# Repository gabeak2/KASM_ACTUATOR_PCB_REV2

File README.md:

A PCBA to drive voice coil actuators at Keck and University of Hawaii at Hilo.  Work done as part of my MS ECE Thesis at Johns Hopkins.  Please enjoy this beautiful glamor shot of my boards !

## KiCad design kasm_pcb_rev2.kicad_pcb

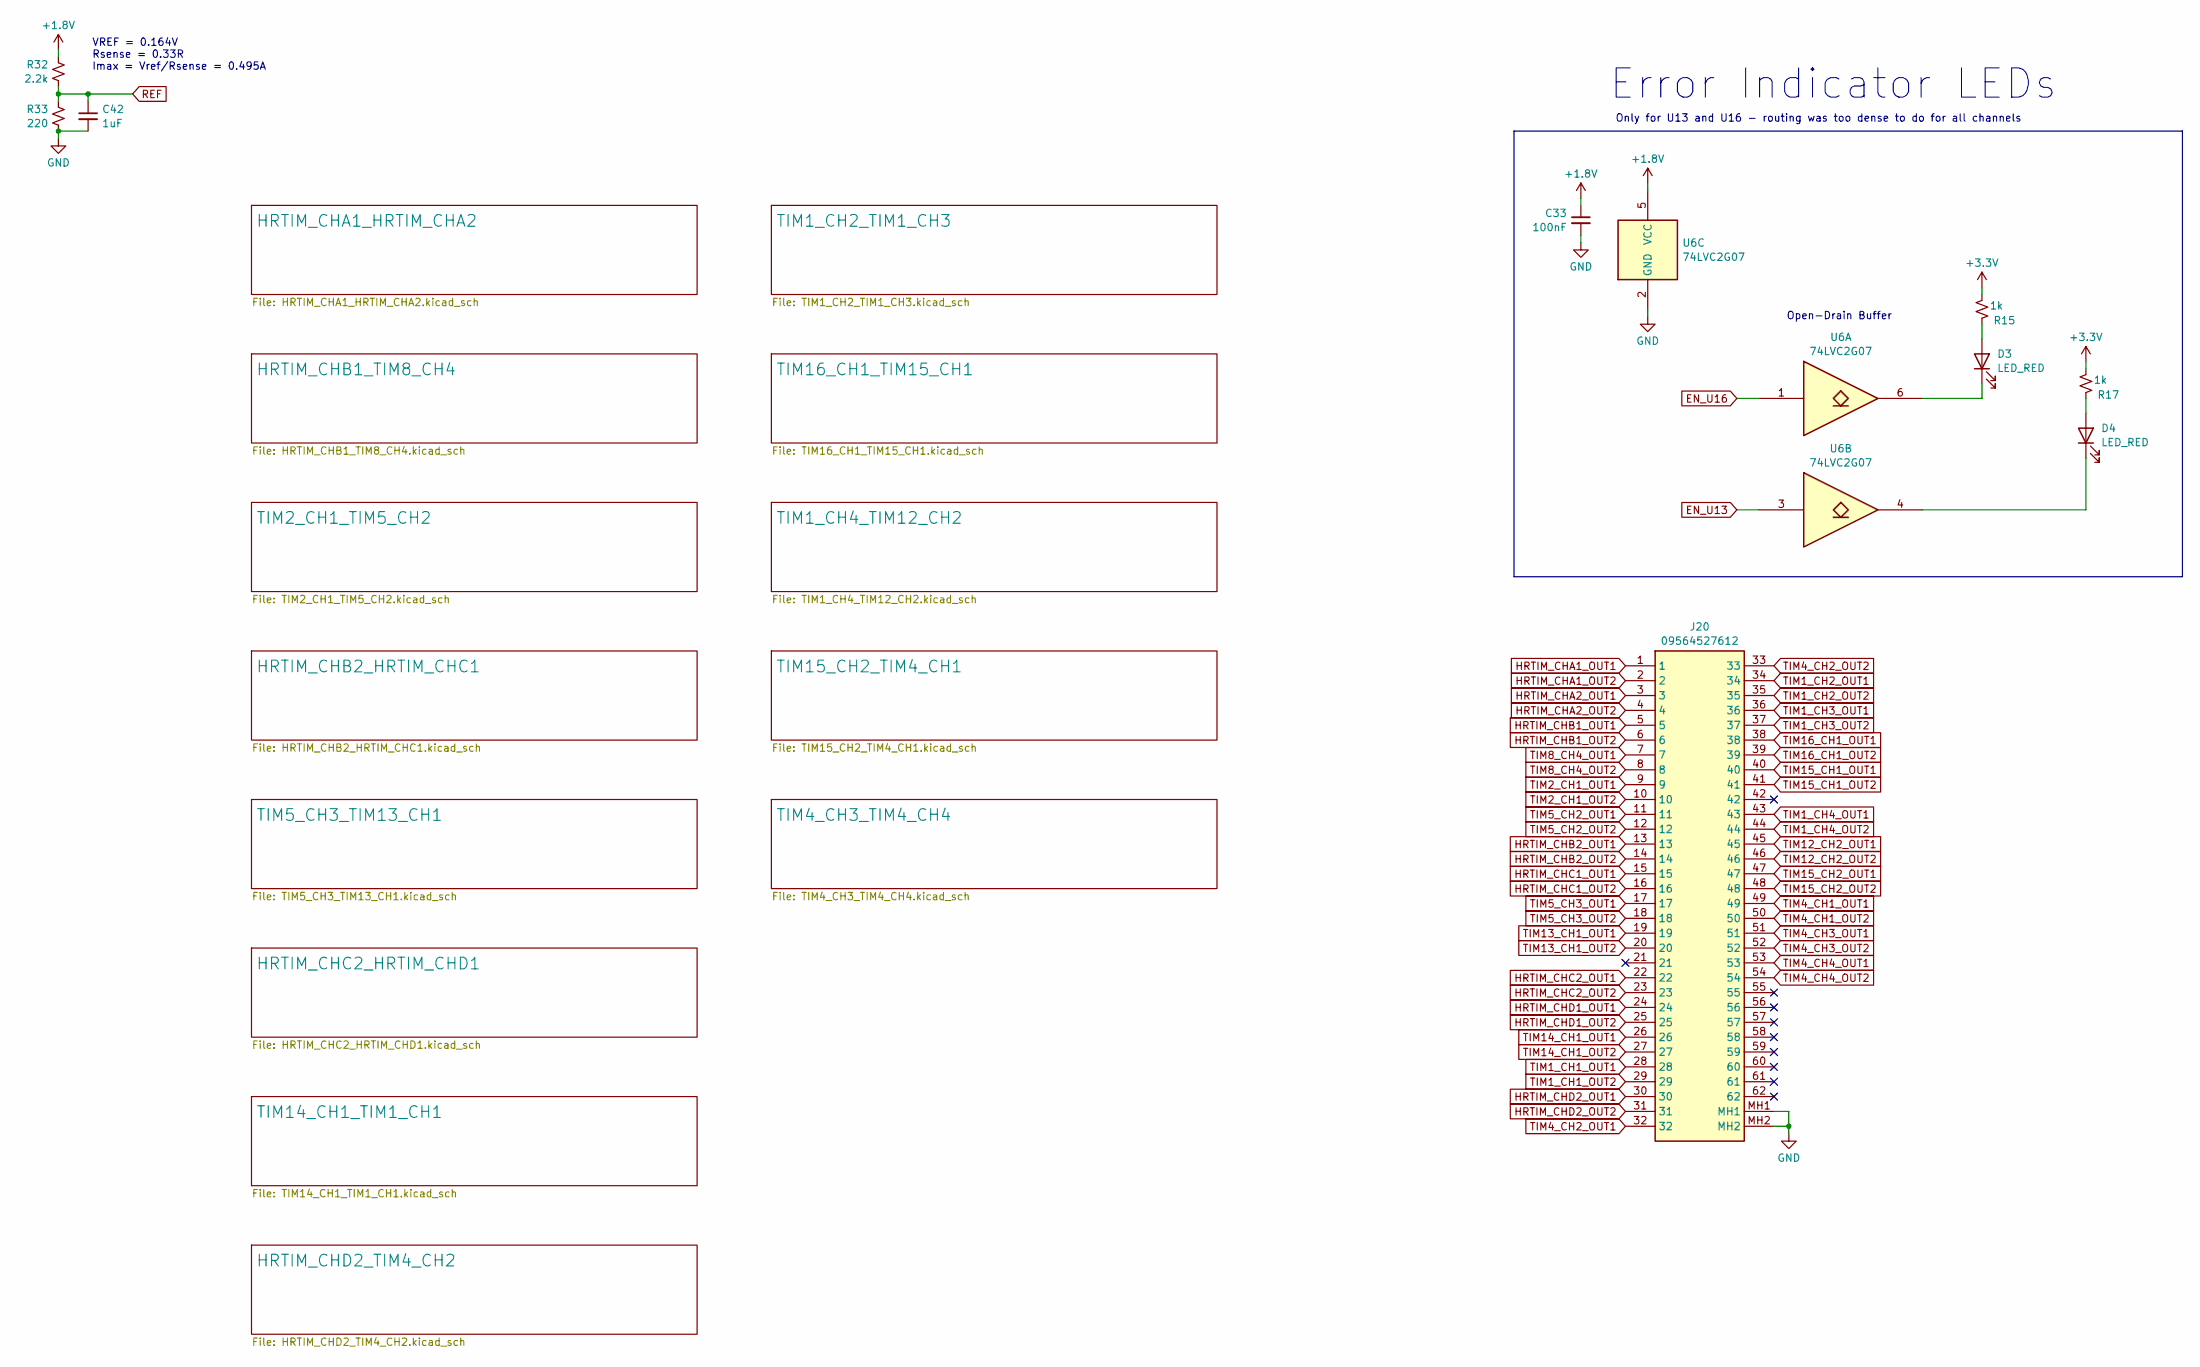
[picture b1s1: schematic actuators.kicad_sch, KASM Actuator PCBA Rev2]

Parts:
C33: 100nF; C_0402_1005Metric; LCSC C1525
C42: 1uF; C_0402_1005Metric; LCSC C52923
D3, D4: LED_RED; LED_0603_1608Metric; LCSC C2286
J20: 09564527612; Manufacturer_Part_Number 09564527612; Mouser Part Number 617-09-56-452-7612
R15, R17: 1k; R_0402_1005Metric; LCSC C11702
R32: 2.2k; R_0402_1005Metric; LCSC C25879
R33: 220; R_0402_1005Metric; LCSC C25091
U6: 74LVC2G07; SOT-23-6; LCSC C37708

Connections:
+1.8V: C33.1, R32.1, U6.5 (VCC); also elsewhere on the board
+3.3V: R15.1, R17.1; also elsewhere on the board
EN_U13: U6.3; also elsewhere on the board
EN_U16: U6.1; also elsewhere on the board
GND: C33.2, C42.2, J20.MH1, J20.MH2, R33.2, U6.2 (GND); also elsewhere on the board
HRTIM_CHA1_OUT1: J20.1; also elsewhere on the board
HRTIM_CHA1_OUT2: J20.2; also elsewhere on the board
HRTIM_CHA2_OUT1: J20.3; also elsewhere on the board
HRTIM_CHA2_OUT2: J20.4; also elsewhere on the board
HRTIM_CHB1_OUT1: J20.5; also elsewhere on the board
HRTIM_CHB1_OUT2: J20.6; also elsewhere on the board
HRTIM_CHB2_OUT1: J20.13; also elsewhere on the board
HRTIM_CHB2_OUT2: J20.14; also elsewhere on the board
HRTIM_CHC1_OUT1: J20.15; also elsewhere on the board
HRTIM_CHC1_OUT2: J20.16; also elsewhere on the board
HRTIM_CHC2_OUT1: J20.22; also elsewhere on the board
HRTIM_CHC2_OUT2: J20.23; also elsewhere on the board
HRTIM_CHD1_OUT1: J20.24; also elsewhere on the board
HRTIM_CHD1_OUT2: J20.25; also elsewhere on the board
HRTIM_CHD2_OUT1: J20.30; also elsewhere on the board
HRTIM_CHD2_OUT2: J20.31; also elsewhere on the board
unnamed: D3.2 (A), R15.2
unnamed: D3.1 (K), U6.6
unnamed: D4.2 (A), R17.2
unnamed: D4.1 (K), U6.4
REF: C42.1, R32.2, R33.1; also elsewhere on the board
TIM1_CH1_OUT1: J20.28; also elsewhere on the board
TIM1_CH1_OUT2: J20.29; also elsewhere on the board
TIM1_CH2_OUT1: J20.34; also elsewhere on the board
TIM1_CH2_OUT2: J20.35; also elsewhere on the board
TIM1_CH3_OUT1: J20.36; also elsewhere on the board
TIM1_CH3_OUT2: J20.37; also elsewhere on the board
TIM1_CH4_OUT1: J20.43; also elsewhere on the board
TIM1_CH4_OUT2: J20.44; also elsewhere on the board
TIM2_CH1_OUT1: J20.9; also elsewhere on the board
TIM2_CH1_OUT2: J20.10; also elsewhere on the board
TIM4_CH1_OUT1: J20.49; also elsewhere on the board
TIM4_CH1_OUT2: J20.50; also elsewhere on the board
TIM4_CH2_OUT1: J20.32; also elsewhere on the board
TIM4_CH2_OUT2: J20.33; also elsewhere on the board
TIM4_CH3_OUT1: J20.51; also elsewhere on the board
TIM4_CH3_OUT2: J20.52; also elsewhere on the board
TIM4_CH4_OUT1: J20.53; also elsewhere on the board
TIM4_CH4_OUT2: J20.54; also elsewhere on the board
TIM5_CH2_OUT1: J20.11; also elsewhere on the board
TIM5_CH2_OUT2: J20.12; also elsewhere on the board
TIM5_CH3_OUT1: J20.17; also elsewhere on the board
TIM5_CH3_OUT2: J20.18; also elsewhere on the board
TIM8_CH4_OUT1: J20.7; also elsewhere on the board
TIM8_CH4_OUT2: J20.8; also elsewhere on the board
TIM12_CH2_OUT1: J20.45; also elsewhere on the board
TIM12_CH2_OUT2: J20.46; also elsewhere on the board
TIM13_CH1_OUT1: J20.19; also elsewhere on the board
TIM13_CH1_OUT2: J20.20; also elsewhere on the board
TIM14_CH1_OUT1: J20.26; also elsewhere on the board
TIM14_CH1_OUT2: J20.27; also elsewhere on the board
TIM15_CH1_OUT1: J20.40; also elsewhere on the board
TIM15_CH1_OUT2: J20.41; also elsewhere on the board
TIM15_CH2_OUT1: J20.47; also elsewhere on the board
TIM15_CH2_OUT2: J20.48; also elsewhere on the board
TIM16_CH1_OUT1: J20.38; also elsewhere on the board
TIM16_CH1_OUT2: J20.39; also elsewhere on the board

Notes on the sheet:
Only for U13 and U16 - routing was too dense to do for all channels
Error Indicator LEDs
Open-Drain Buffer
VREF = 0.164V Rsense = 0.33R Imax = Vref/Rsense = 0.495A

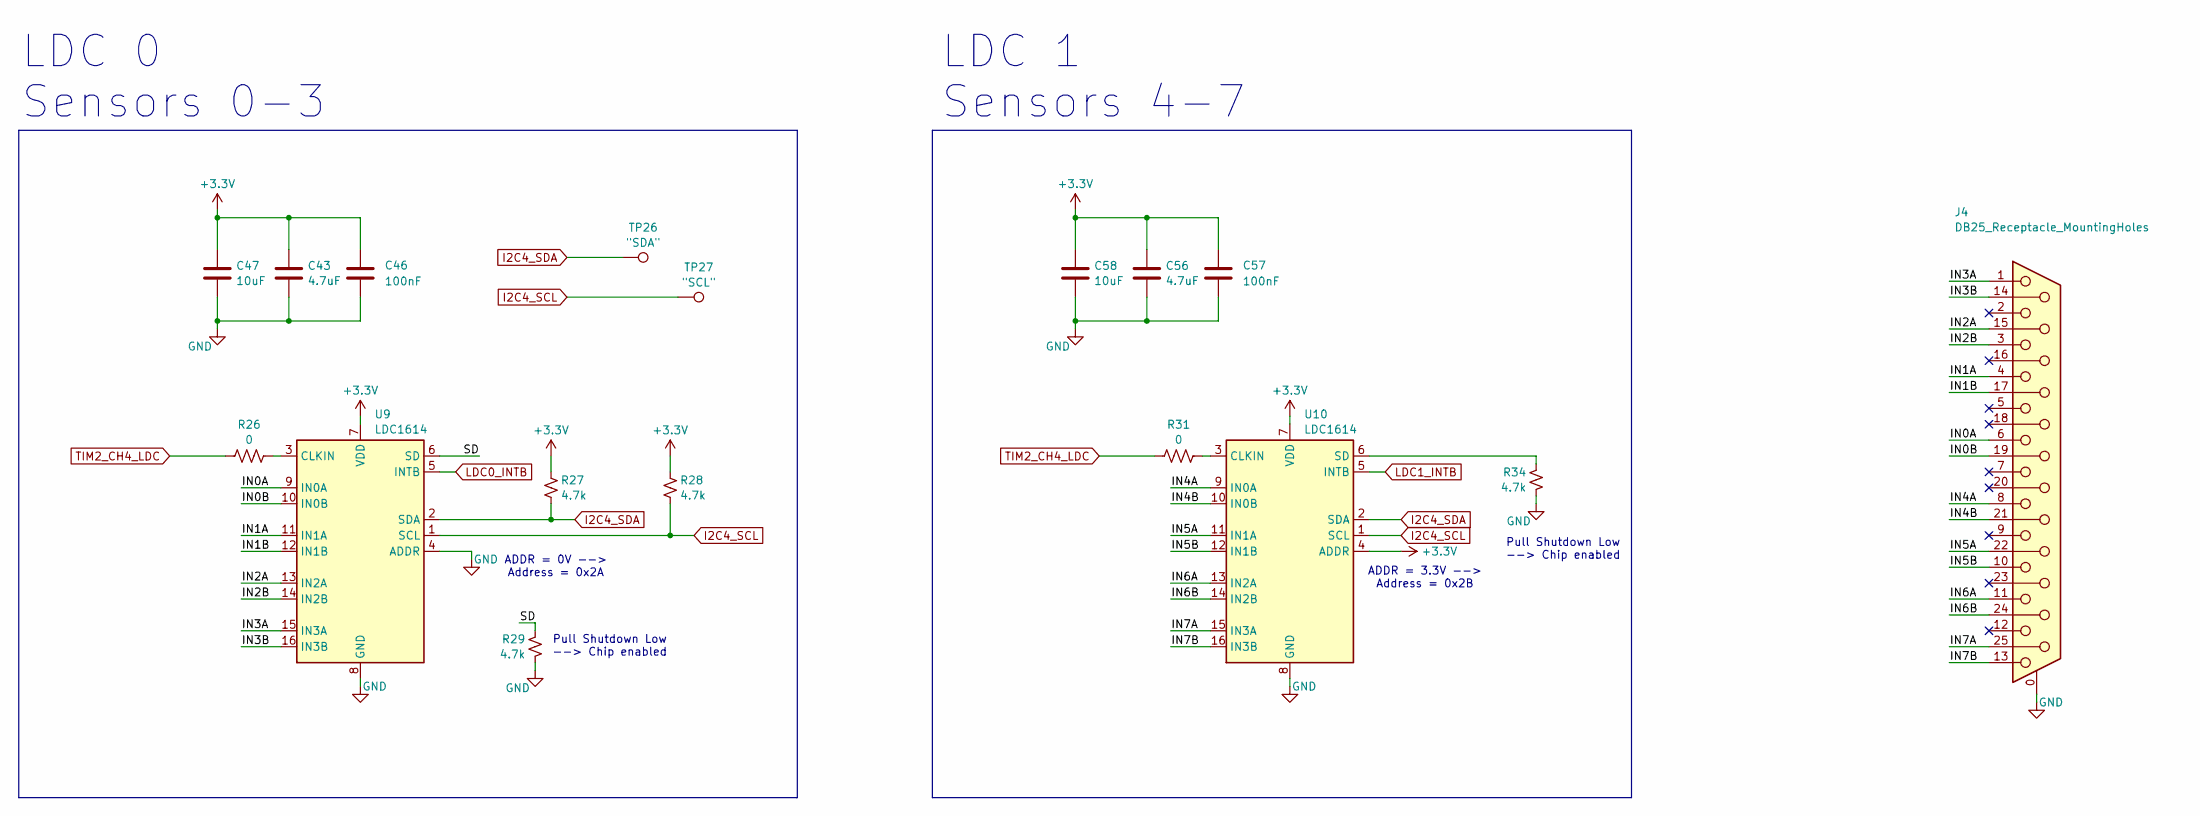
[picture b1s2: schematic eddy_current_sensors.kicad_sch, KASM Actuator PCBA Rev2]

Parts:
C43, C56: 4.7uF; C_0402_1005Metric; LCSC C23733
C46, C57: 100nF; C_0402_1005Metric; LCSC C307331
C47, C58: 10uF; C_0805_2012Metric; LCSC C440198
J4: DB25_Receptacle_MountingHoles; TE_5747846-4
R26, R31: 0; R_0402_1005Metric; LCSC C17168
R27, R28, R29, R34: 4.7k; R_0402_1005Metric; LCSC C25900
TP26: "SDA"; TestPoint_THTPad_D1.0mm_Drill0.5mm
TP27: "SCL"; TestPoint_THTPad_D1.0mm_Drill0.5mm
U9, U10: LDC1614; WQFN-16-1EP_4x4mm_P0.5mm_EP2.6x2.6mm; LCSC C968448

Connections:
+3.3V: C43.1, C46.1, C47.1, C56.1, C57.1, C58.1, R27.1, R28.1, U9.7 (VDD), U10.4 (ADDR), U10.7 (VDD); also elsewhere on the board
/Eddy Current Sensors/IN0A: J4.6, U9.9 (IN0A)
/Eddy Current Sensors/IN0B: J4.19, U9.10 (IN0B)
/Eddy Current Sensors/IN1A: J4.4, U9.11 (IN1A)
/Eddy Current Sensors/IN1B: J4.17, U9.12 (IN1B)
/Eddy Current Sensors/IN2A: J4.15, U9.13 (IN2A)
/Eddy Current Sensors/IN2B: J4.3, U9.14 (IN2B)
/Eddy Current Sensors/IN3A: J4.1, U9.15 (IN3A)
/Eddy Current Sensors/IN3B: J4.14, U9.16 (IN3B)
/Eddy Current Sensors/IN4A: J4.8, U10.9 (IN0A)
/Eddy Current Sensors/IN4B: J4.21, U10.10 (IN0B)
/Eddy Current Sensors/IN5A: J4.22, U10.11 (IN1A)
/Eddy Current Sensors/IN5B: J4.10, U10.12 (IN1B)
/Eddy Current Sensors/IN6A: J4.11, U10.13 (IN2A)
/Eddy Current Sensors/IN6B: J4.24, U10.14 (IN2B)
/Eddy Current Sensors/IN7A: J4.25, U10.15 (IN3A)
/Eddy Current Sensors/IN7B: J4.13, U10.16 (IN3B)
/Eddy Current Sensors/SD: R29.1, U9.6 (SD)
GND: C43.2, C46.2, C47.2, C56.2, C57.2, C58.2, J4.0 (PAD), R29.2, R34.2, U9.4 (ADDR), U9.8 (GND), U9.17 (GND), U10.8 (GND), U10.17 (GND); also elsewhere on the board
I2C4_SCL: R28.2, TP27.1, U9.1 (SCL), U10.1 (SCL); also elsewhere on the board
I2C4_SDA: R27.2, TP26.1, U9.2 (SDA), U10.2 (SDA); also elsewhere on the board
LDC0_INTB: U9.5 (INTB); also elsewhere on the board
LDC1_INTB: U10.5 (INTB); also elsewhere on the board
unnamed: R26.1, U9.3 (CLKIN)
unnamed: R31.1, U10.3 (CLKIN)
unnamed: R34.1, U10.6 (SD)
TIM2_CH4_LDC: R26.2, R31.2; also elsewhere on the board

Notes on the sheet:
Pull Shutdown Low --> Chip enabled
LDC 0 Sensors 0-3
LDC 1 Sensors 4-7
ADDR = 3.3V --> Address = 0x2B
ADDR = 0V --> Address = 0x2A

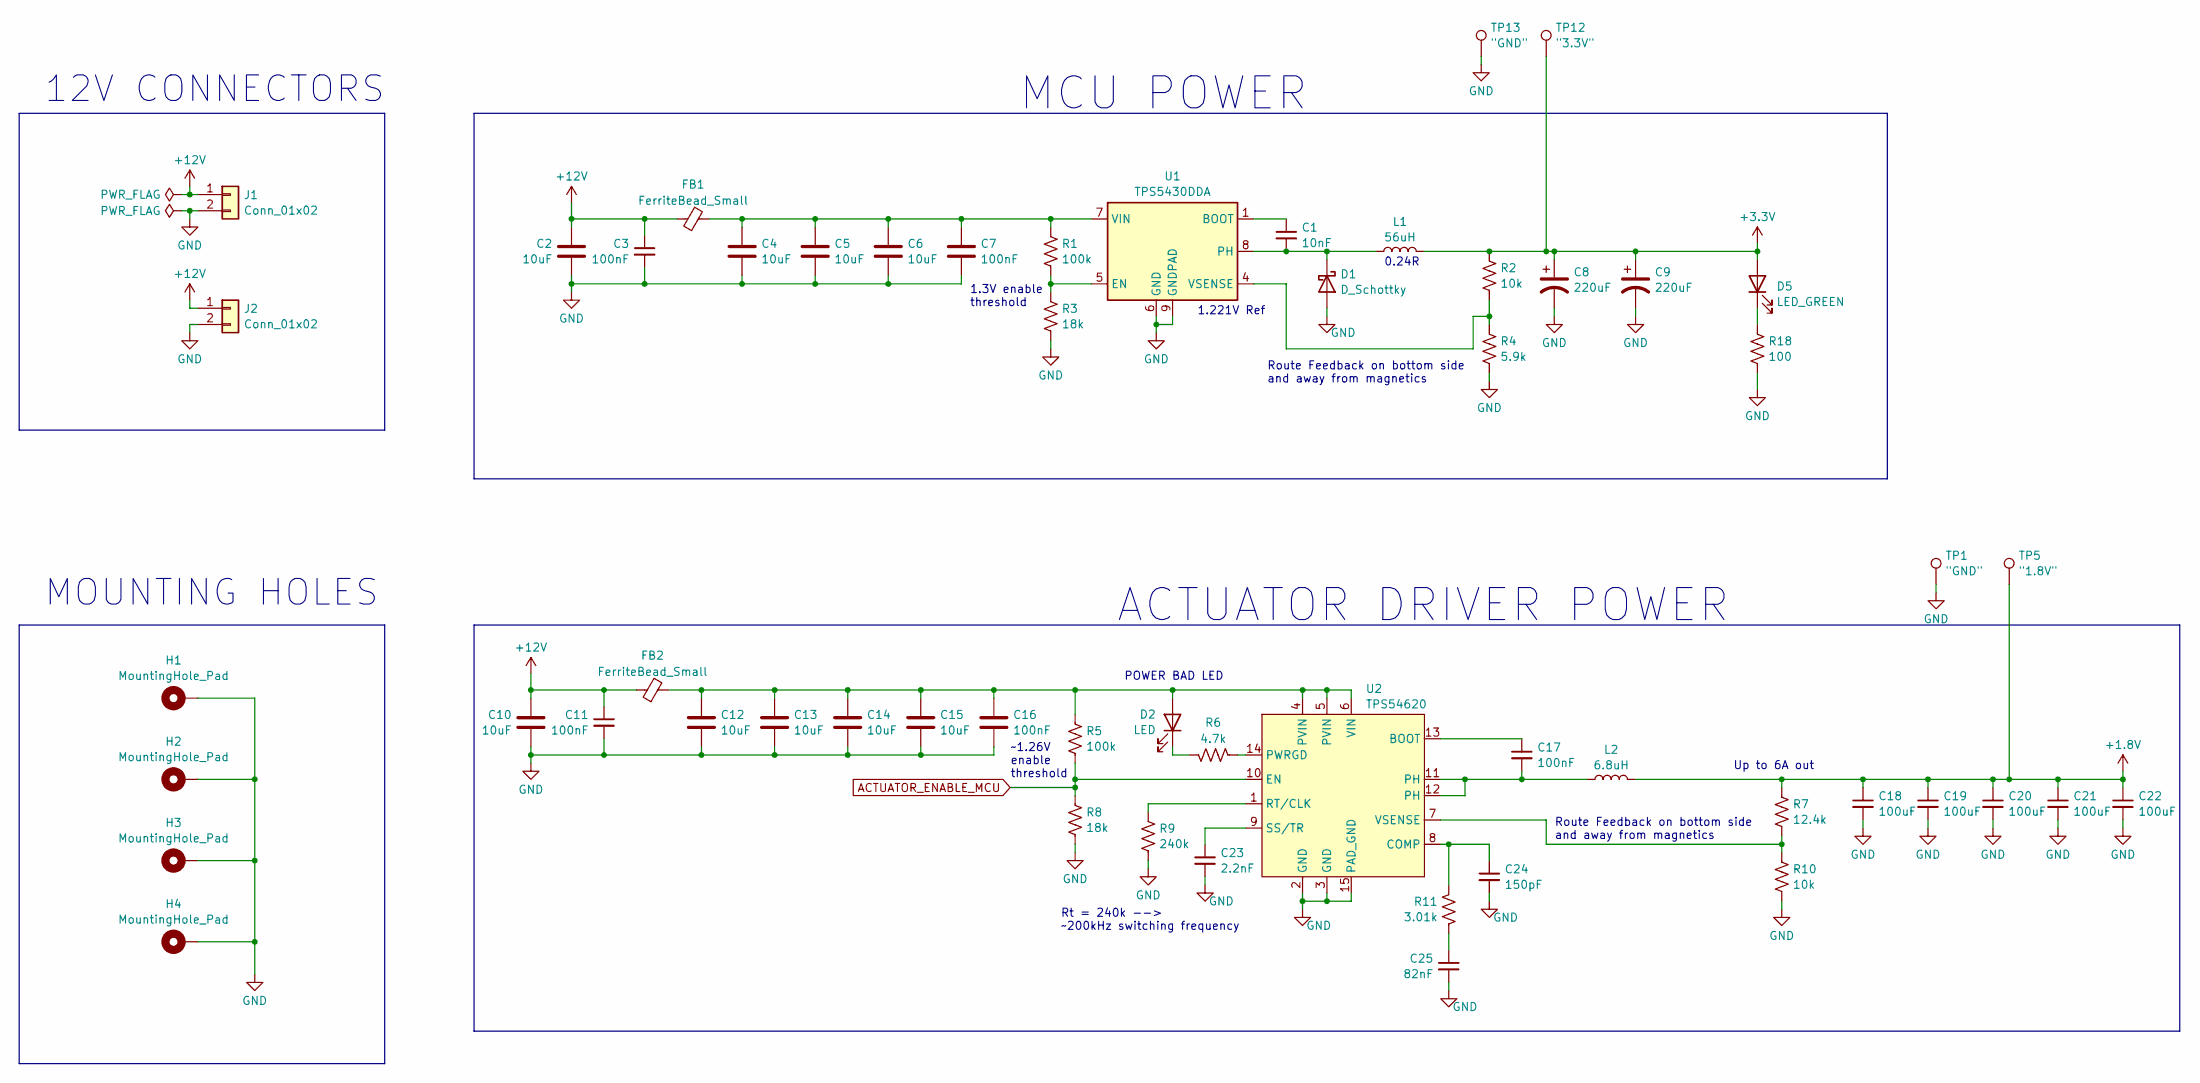
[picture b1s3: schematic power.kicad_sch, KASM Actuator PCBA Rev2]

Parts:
C1: 10nF; C_0402_1005Metric; LCSC C60133
C2, C4, C5, C6, C10, C12, C13, C14, C15: 10uF; C_1206_3216Metric; LCSC C454102
C3, C7, C11, C16, C17: 100nF; C_0402_1005Metric; LCSC C1525
C8, C9: 220uF; CP_Elec_6.3x5.4; LCSC C59953
C18, C19, C20, C21, C22: 100uF; C_1206_3216Metric; LCSC C15008
C23: 2.2nF; C_0402_1005Metric; LCSC C1531
C24: 150pF; C_0402_1005Metric; LCSC C106998
C25: 82nF; C_0402_1005Metric; LCSC C524617
D1: D_Schottky; D_SOD-323; LCSC C191023
D2: LED; LED_0603_1608Metric; LCSC C2286
D5: LED_GREEN; LED_0603_1608Metric; LCSC C965804
FB1, FB2: FerriteBead_Small; L_0805_2012Metric; LCSC C1017
H1, H2, H3, H4: MountingHole_Pad; MountingHole_3.2mm_M3_DIN965_Pad
J1, J2: Conn_01x02; Molex_KK-396_A-41792-0002_1x02_P3.96mm_Horizontal
L1: 56uH; L_Changjiang_FNR5020S; LCSC C167944
L2: 6.8uH; L_Chilisin_BMRF00101040; LCSC C167231
R1, R5: 100k; R_0402_1005Metric; LCSC C25741
R2, R10: 10k; R_0402_1005Metric; LCSC C25744
R3, R8: 18k; R_0402_1005Metric; LCSC C138044
R4: 5.9k; R_0402_1005Metric; LCSC C270591
R6: 4.7k; R_0402_1005Metric; LCSC C25900
R7: 12.4k; R_0402_1005Metric; LCSC C11692
R9: 240k; R_0402_1005Metric; LCSC C138030
R11: 3.01k; R_0402_1005Metric; LCSC C137994
R18: 100; R_0402_1005Metric; LCSC C106232
TP1, TP13: "GND"; TestPoint_THTPad_1.0x1.0mm_Drill0.5mm
TP5: "1.8V"; TestPoint_THTPad_1.0x1.0mm_Drill0.5mm
TP12: "3.3V"; TestPoint_THTPad_1.0x1.0mm_Drill0.5mm
U1: TPS5430DDA; TI_SO-PowerPAD-8_ThermalVias; LCSC C9864
U2: TPS54620; Texas_S-PVQFN-N14_ThermalVias; LCSC C29438

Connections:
+1.8V: C18.1, C19.1, C20.1, C21.1, C22.1, L2.2, R7.1, TP5.1; also elsewhere on the board
+3.3V: C8.1, C9.1, D5.2 (A), L1.2, R2.1, TP12.1; also elsewhere on the board
+12V: C2.1, C3.1, C10.1, C11.1, FB1.1, FB2.1, J1.1, J2.1
ACTUATOR_ENABLE_MCU: R5.2, R8.1, U2.10 (EN); also elsewhere on the board
GND: C2.2, C3.2, C4.2, C5.2, C6.2, C7.2, C8.2, C9.2, C10.2, C11.2, C12.2, C13.2, C14.2, C15.2, C16.2, C18.2, C19.2, C20.2, C21.2, C22.2, C23.2, C24.2, C25.2, D1.2 (A), H1.1, H2.1, H3.1, H4.1, J1.2, J2.2, R3.2, R4.2, R8.2, R9.2, R10.2, R18.2, TP1.1, TP13.1, U1.6 (GND), U1.9 (GNDPAD), U2.2 (GND), U2.3 (GND), U2.15 (PAD_GND); also elsewhere on the board
unnamed: C17.2, L2.1, U2.11 (PH), U2.12 (PH)
unnamed: C25.1, R11.2
unnamed: C1.2, D1.1 (K), L1.1, U1.8 (PH)
unnamed: C12.1, C13.1, C14.1, C15.1, C16.1, D2.2 (A), FB2.2, R5.1, U2.4 (PVIN), U2.5 (PVIN), U2.6 (VIN)
unnamed: D2.1 (K), R6.2
unnamed: D5.1 (K), R18.1
unnamed: C1.1, U1.1 (BOOT)
unnamed: R1.2, R3.1, U1.5 (EN)
unnamed: C4.1, C5.1, C6.1, C7.1, FB1.2, R1.1, U1.7 (VIN)
unnamed: R2.2, R4.1, U1.4 (VSENSE)
unnamed: C17.1, U2.13 (BOOT)
unnamed: C24.1, R11.1, U2.8 (COMP)
unnamed: R6.1, U2.14 (PWRGD)
unnamed: R9.1, U2.1 (RT/CLK)
unnamed: C23.1, U2.9 (SS/TR)
unnamed: R7.2, R10.1, U2.7 (VSENSE)

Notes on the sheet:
Up to 6A out
1.221V Ref
Rt = 240k --> ~200kHz switching frequency
1.3V enable threshold
Route Feedback on bottom side and away from magnetics
ACTUATOR DRIVER POWER
~1.26V enable threshold
0.24R
POWER BAD LED
12V CONNECTORS
MCU POWER
MOUNTING HOLES

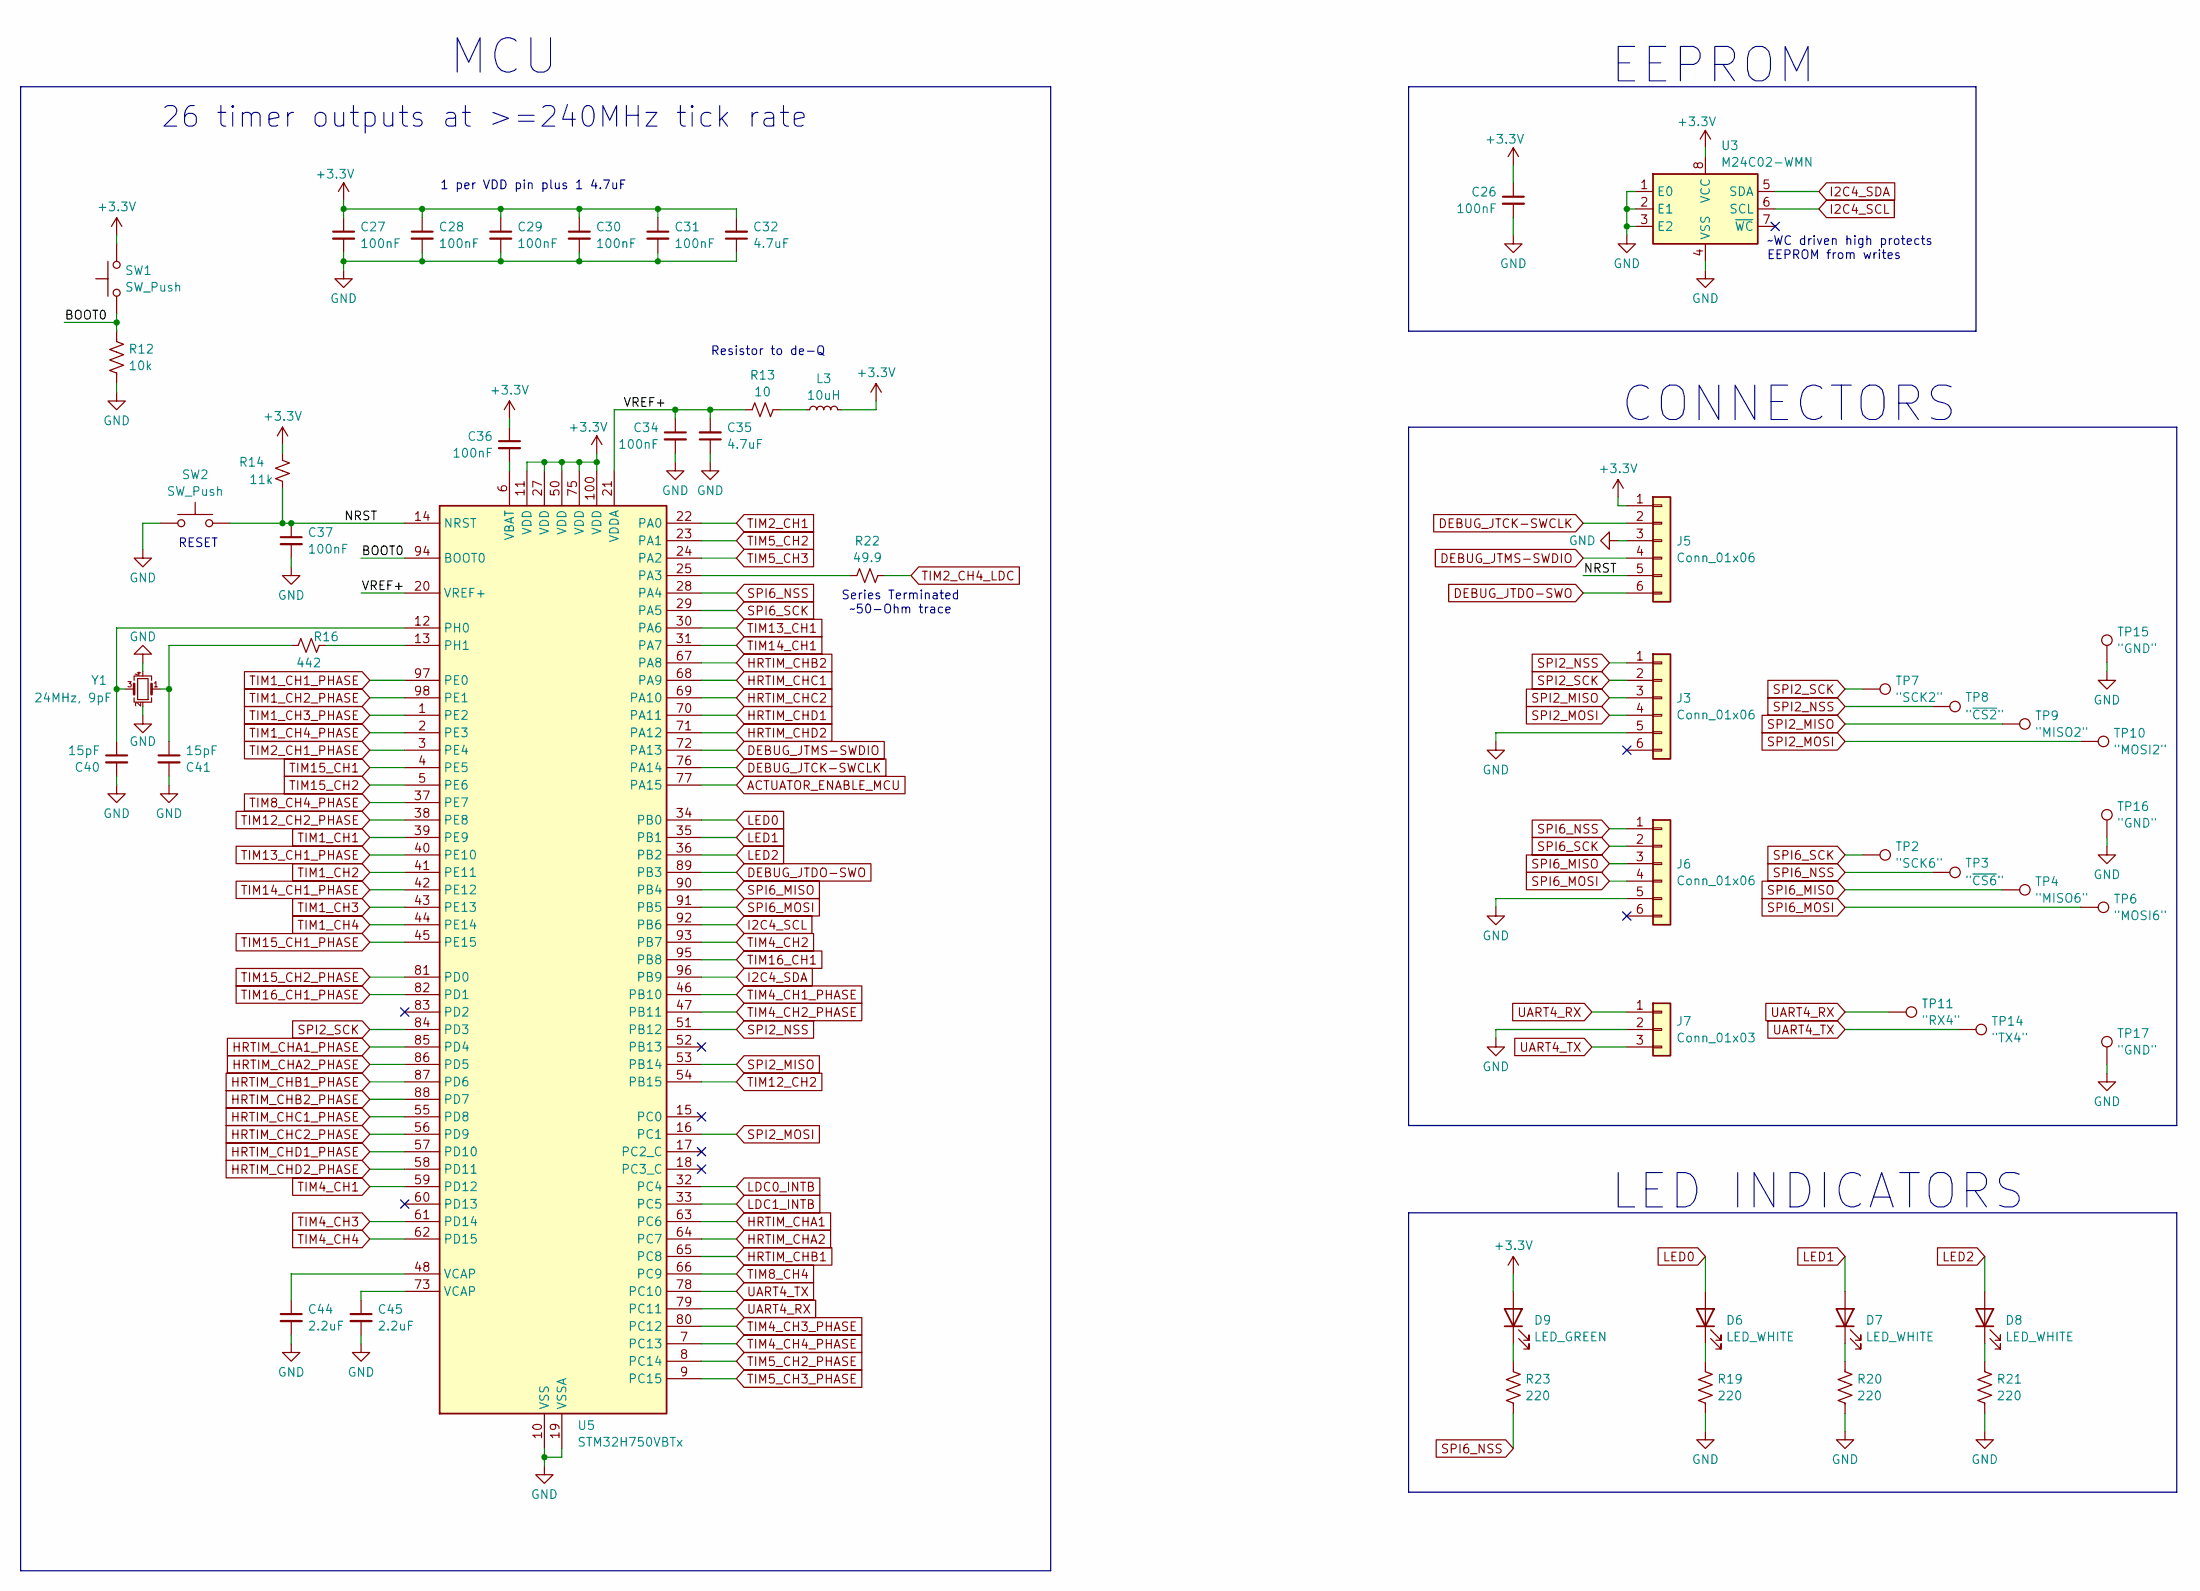
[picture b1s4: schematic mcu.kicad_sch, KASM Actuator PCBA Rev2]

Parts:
C26, C27, C28, C29, C30, C31, C34, C36, C37: 100nF; C_0402_1005Metric; LCSC C1525
C32, C35: 4.7uF; C_0402_1005Metric; LCSC C23733
C40, C41: 15pF; C_0402_1005Metric; LCSC C1548
C44, C45: 2.2uF; C_0402_1005Metric; LCSC C12530
D6, D7, D8: LED_WHITE; LED_0402_1005Metric; LCSC C20613596
D9: LED_GREEN; LED_0603_1608Metric; LCSC C965804
J3, J5: Conn_01x06; PinHeader_1x06_P2.54mm_Vertical
J6: Conn_01x06; CONN_A-7478-06A_MOL
J7: Conn_01x03; PinHeader_1x03_P2.54mm_Vertical
L3: 10uH; L_0603_1608Metric; LCSC C51942
R12: 10k; R_0402_1005Metric; LCSC C25744
R13: 10; R_0402_1005Metric; LCSC C409845
R14: 11k; R_0402_1005Metric; LCSC C25749
R16: 442; R_0402_1005Metric; LCSC C126137
R19, R20, R21, R23: 220; R_0402_1005Metric; LCSC C25091
R22: 49.9; R_0402_1005Metric; LCSC C144754
SW1, SW2: SW_Push; SW_Push_1P1T_XKB_TS-1187A; LCSC C318884
TP2: "SCK6"; TestPoint_THTPad_1.0x1.0mm_Drill0.5mm
TP3: "~{CS6}"; TestPoint_THTPad_1.0x1.0mm_Drill0.5mm
TP4: "MISO6"; TestPoint_THTPad_1.0x1.0mm_Drill0.5mm
TP6: "MOSI6"; TestPoint_THTPad_1.0x1.0mm_Drill0.5mm
TP7: "SCK2"; TestPoint_THTPad_1.0x1.0mm_Drill0.5mm
TP8: "~{CS2}"; TestPoint_THTPad_1.0x1.0mm_Drill0.5mm
TP9: "MISO2"; TestPoint_THTPad_1.0x1.0mm_Drill0.5mm
TP10: "MOSI2"; TestPoint_THTPad_1.0x1.0mm_Drill0.5mm
TP11: "RX4"; TestPoint_THTPad_1.0x1.0mm_Drill0.5mm
TP14: "TX4"; TestPoint_THTPad_1.0x1.0mm_Drill0.5mm
TP15, TP16, TP17: "GND"; TestPoint_THTPad_1.0x1.0mm_Drill0.5mm
U3: M24C02-WMN; SOIC-8_3.9x4.9mm_P1.27mm; LCSC C7562
U5: STM32H750VBTx; LQFP-100_14x14mm_P0.5mm; LCSC C404010
Y1: 24MHz, 9pF; Crystal_SMD_SeikoEpson_FA128-4Pin_2.0x1.6mm; LCSC C2929399

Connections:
+3.3V: C26.1, C27.1, C28.1, C29.1, C30.1, C31.1, C32.2, C36.1, D9.2 (A), J5.1, L3.2, R14.1, SW1.2, U3.8 (VCC), U5.11 (VDD), U5.27 (VDD), U5.50 (VDD), U5.75 (VDD), U5.100 (VDD); also elsewhere on the board
/MCU/BOOT0: R12.1, SW1.1, U5.94 (BOOT0)
/MCU/NRST: C37.1, J5.5, R14.2, SW2.2, U5.14 (NRST)
/MCU/VREF+: C34.1, C35.2, R13.1, U5.20 (VREF+), U5.21 (VDDA)
ACTUATOR_ENABLE_MCU: U5.77 (PA15); also elsewhere on the board
DEBUG_JTCK-SWCLK: J5.2, U5.76 (PA14)
DEBUG_JTDO-SWO: J5.6, U5.89 (PB3)
DEBUG_JTMS-SWDIO: J5.4, U5.72 (PA13)
GND: C26.2, C27.2, C28.2, C29.2, C30.2, C31.2, C32.1, C34.2, C35.1, C37.2, C40.2, C41.2, C44.2, C45.2, J3.5, J5.3, J6.5, J7.2, R12.2, R19.2, R20.2, R21.2, SW2.1, TP15.1, TP16.1, TP17.1, U3.1 (E0), U3.2 (E1), U3.3 (E2), U3.4 (VSS), U5.10 (VSS), U5.19 (VSSA), U5.26 (VSS), U5.49 (VSS), U5.74 (VSS), U5.99 (VSS), Y1.2, Y1.4; also elsewhere on the board
HRTIM_CHA1: U5.63 (PC6); also elsewhere on the board
HRTIM_CHA1_PHASE: U5.85 (PD4); also elsewhere on the board
HRTIM_CHA2: U5.64 (PC7); also elsewhere on the board
HRTIM_CHA2_PHASE: U5.86 (PD5); also elsewhere on the board
HRTIM_CHB1: U5.65 (PC8); also elsewhere on the board
HRTIM_CHB1_PHASE: U5.87 (PD6); also elsewhere on the board
HRTIM_CHB2: U5.67 (PA8); also elsewhere on the board
HRTIM_CHB2_PHASE: U5.88 (PD7); also elsewhere on the board
HRTIM_CHC1: U5.68 (PA9); also elsewhere on the board
HRTIM_CHC1_PHASE: U5.55 (PD8); also elsewhere on the board
HRTIM_CHC2: U5.69 (PA10); also elsewhere on the board
HRTIM_CHC2_PHASE: U5.56 (PD9); also elsewhere on the board
HRTIM_CHD1: U5.70 (PA11); also elsewhere on the board
HRTIM_CHD1_PHASE: U5.57 (PD10); also elsewhere on the board
HRTIM_CHD2: U5.71 (PA12); also elsewhere on the board
HRTIM_CHD2_PHASE: U5.58 (PD11); also elsewhere on the board
I2C4_SCL: U3.6 (SCL), U5.92 (PB6); also elsewhere on the board
I2C4_SDA: U3.5 (SDA), U5.96 (PB9); also elsewhere on the board
LDC0_INTB: U5.32 (PC4); also elsewhere on the board
LDC1_INTB: U5.33 (PC5); also elsewhere on the board
LED0: D6.2 (A), U5.34 (PB0)
LED1: D7.2 (A), U5.35 (PB1)
LED2: D8.2 (A), U5.36 (PB2)
unnamed: C41.1, R16.1, Y1.1
unnamed: C44.1, U5.48 (VCAP)
unnamed: C45.1, U5.73 (VCAP)
unnamed: D6.1 (K), R19.1
unnamed: D7.1 (K), R20.1
unnamed: D8.1 (K), R21.1
unnamed: D9.1 (K), R23.1
unnamed: L3.1, R13.2
unnamed: R22.1, U5.25 (PA3)
unnamed: C40.1, U5.12 (PH0), Y1.3
unnamed: R16.2, U5.13 (PH1)
unnamed: C36.2, U5.6 (VBAT)
SPI2_MISO: J3.3, TP9.1, U5.53 (PB14)
SPI2_MOSI: J3.4, TP10.1, U5.16 (PC1)
SPI2_NSS: J3.1, TP8.1, U5.51 (PB12)
SPI2_SCK: J3.2, TP7.1, U5.84 (PD3)
SPI6_MISO: J6.3, TP4.1, U5.90 (PB4)
SPI6_MOSI: J6.4, TP6.1, U5.91 (PB5)
SPI6_NSS: J6.1, R23.2, TP3.1, U5.28 (PA4)
SPI6_SCK: J6.2, TP2.1, U5.29 (PA5)
TIM1_CH1: U5.39 (PE9); also elsewhere on the board
TIM1_CH1_PHASE: U5.97 (PE0); also elsewhere on the board
TIM1_CH2: U5.41 (PE11); also elsewhere on the board
TIM1_CH2_PHASE: U5.98 (PE1); also elsewhere on the board
TIM1_CH3: U5.43 (PE13); also elsewhere on the board
TIM1_CH3_PHASE: U5.1 (PE2); also elsewhere on the board
TIM1_CH4: U5.44 (PE14); also elsewhere on the board
TIM1_CH4_PHASE: U5.2 (PE3); also elsewhere on the board
TIM2_CH1: U5.22 (PA0); also elsewhere on the board
TIM2_CH1_PHASE: U5.3 (PE4); also elsewhere on the board
TIM2_CH4_LDC: R22.2; also elsewhere on the board
TIM4_CH1: U5.59 (PD12); also elsewhere on the board
TIM4_CH1_PHASE: U5.46 (PB10); also elsewhere on the board
TIM4_CH2: U5.93 (PB7); also elsewhere on the board
TIM4_CH2_PHASE: U5.47 (PB11); also elsewhere on the board
TIM4_CH3: U5.61 (PD14); also elsewhere on the board
TIM4_CH3_PHASE: U5.80 (PC12); also elsewhere on the board
TIM4_CH4: U5.62 (PD15); also elsewhere on the board
TIM4_CH4_PHASE: U5.7 (PC13); also elsewhere on the board
TIM5_CH2: U5.23 (PA1); also elsewhere on the board
TIM5_CH2_PHASE: U5.8 (PC14); also elsewhere on the board
TIM5_CH3: U5.24 (PA2); also elsewhere on the board
TIM5_CH3_PHASE: U5.9 (PC15); also elsewhere on the board
TIM8_CH4: U5.66 (PC9); also elsewhere on the board
TIM8_CH4_PHASE: U5.37 (PE7); also elsewhere on the board
TIM12_CH2: U5.54 (PB15); also elsewhere on the board
TIM12_CH2_PHASE: U5.38 (PE8); also elsewhere on the board
TIM13_CH1: U5.30 (PA6); also elsewhere on the board
TIM13_CH1_PHASE: U5.40 (PE10); also elsewhere on the board
TIM14_CH1: U5.31 (PA7); also elsewhere on the board
TIM14_CH1_PHASE: U5.42 (PE12); also elsewhere on the board
TIM15_CH1: U5.4 (PE5); also elsewhere on the board
TIM15_CH1_PHASE: U5.45 (PE15); also elsewhere on the board
TIM15_CH2: U5.5 (PE6); also elsewhere on the board
TIM15_CH2_PHASE: U5.81 (PD0); also elsewhere on the board
TIM16_CH1: U5.95 (PB8); also elsewhere on the board
TIM16_CH1_PHASE: U5.82 (PD1); also elsewhere on the board
UART4_RX: J7.1, TP11.1, U5.79 (PC11)
UART4_TX: J7.3, TP14.1, U5.78 (PC10)

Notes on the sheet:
~WC driven high protects EEPROM from writes
CONNECTORS
RESET
26 timer outputs at >=240MHz tick rate
Series Terminated ~50-Ohm trace
Resistor to de-Q
MCU
LED INDICATORS
EEPROM
1 per VDD pin plus 1 4.7uF

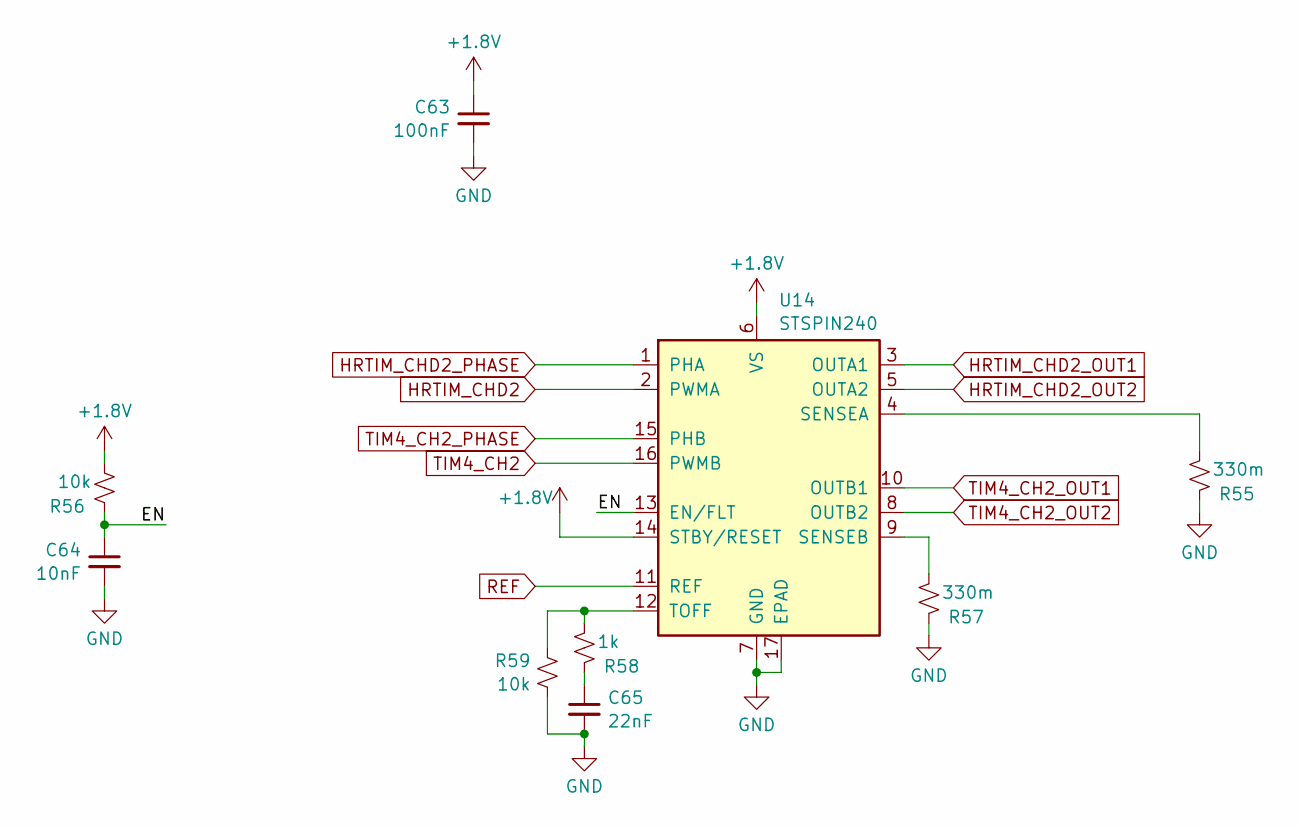
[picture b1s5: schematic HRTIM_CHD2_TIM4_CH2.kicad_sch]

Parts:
C63: 100nF; C_0402_1005Metric; LCSC C1525
C64: 10nF; C_0402_1005Metric; LCSC C15195
C65: 22nF; C_0402_1005Metric; LCSC C1532
R55, R57: 330m; R_0402_1005Metric; LCSC C332660
R56, R59: 10k; R_0402_1005Metric; LCSC C25744
R58: 1k; R_0402_1005Metric; LCSC C11702
U14: STSPIN240; VQFN-16-1EP_3x3mm_P0.5mm_EP1.8x1.8mm; LCSC C962258

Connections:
+1.8V: C63.1, R56.1, U14.6 (VS), U14.14 (STBY/RESET); also elsewhere on the board
/Actuators/HRTIM_CHD2_TIM4_CH2/EN: C64.1, R56.2, U14.13 (EN/FLT)
GND: C63.2, C64.2, C65.2, R55.2, R57.2, R59.2, U14.7 (GND), U14.17 (EPAD); also elsewhere on the board
HRTIM_CHD2: U14.2 (PWMA); also elsewhere on the board
HRTIM_CHD2_OUT1: U14.3 (OUTA1); also elsewhere on the board
HRTIM_CHD2_OUT2: U14.5 (OUTA2); also elsewhere on the board
HRTIM_CHD2_PHASE: U14.1 (PHA); also elsewhere on the board
unnamed: C65.1, R58.2
unnamed: R55.1, U14.4 (SENSEA)
unnamed: R57.1, U14.9 (SENSEB)
unnamed: R58.1, R59.1, U14.12 (TOFF)
REF: U14.11 (REF); also elsewhere on the board
TIM4_CH2: U14.16 (PWMB); also elsewhere on the board
TIM4_CH2_OUT1: U14.10 (OUTB1); also elsewhere on the board
TIM4_CH2_OUT2: U14.8 (OUTB2); also elsewhere on the board
TIM4_CH2_PHASE: U14.15 (PHB); also elsewhere on the board
